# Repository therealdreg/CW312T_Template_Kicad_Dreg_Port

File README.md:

# CW312T_Template_Kicad_Dreg_Port

chipwhisper CW312T template for KiCad with Dreg port (and easyeda file to import)

------

## PCB specs

- Thickness: 1.6 mm (0.062"). Required by the CW312 card-edge connector (Samtec MECF), and it's the default thickness anyway, so no extra cost.
- Edge fingers: ENIG + "gold fingers" (solder mask removed over the pads) is enough for a target plugged in/out a few dozen times. Note JLCPCB only does "gold fingers" with ENIG selected, this is NOT real electroplated hard gold. Use real hard gold (e.g. PCBWay) only if you need hundreds/thousands of insertions.
- Bevel/chamfer (30°): JLCPCB won't bevel boards smaller than 50 x 50 mm, and can't bevel V-cut panelized fingers. Fine to skip on small targets, the MECF socket has its own lead-in.

-----

# kicad project 

[CW312T_Template_Kicad_Dreg_Port.zip](CW312T_Template_Kicad_Dreg_Port.zip)

------

# easyeda pro file to import

[ProPrj_CW312T_Template_Kicad_Dreg_Port_2026-06-29.epro2](ProPrj_CW312T_Template_Kicad_Dreg_Port_2026-06-29.epro2)

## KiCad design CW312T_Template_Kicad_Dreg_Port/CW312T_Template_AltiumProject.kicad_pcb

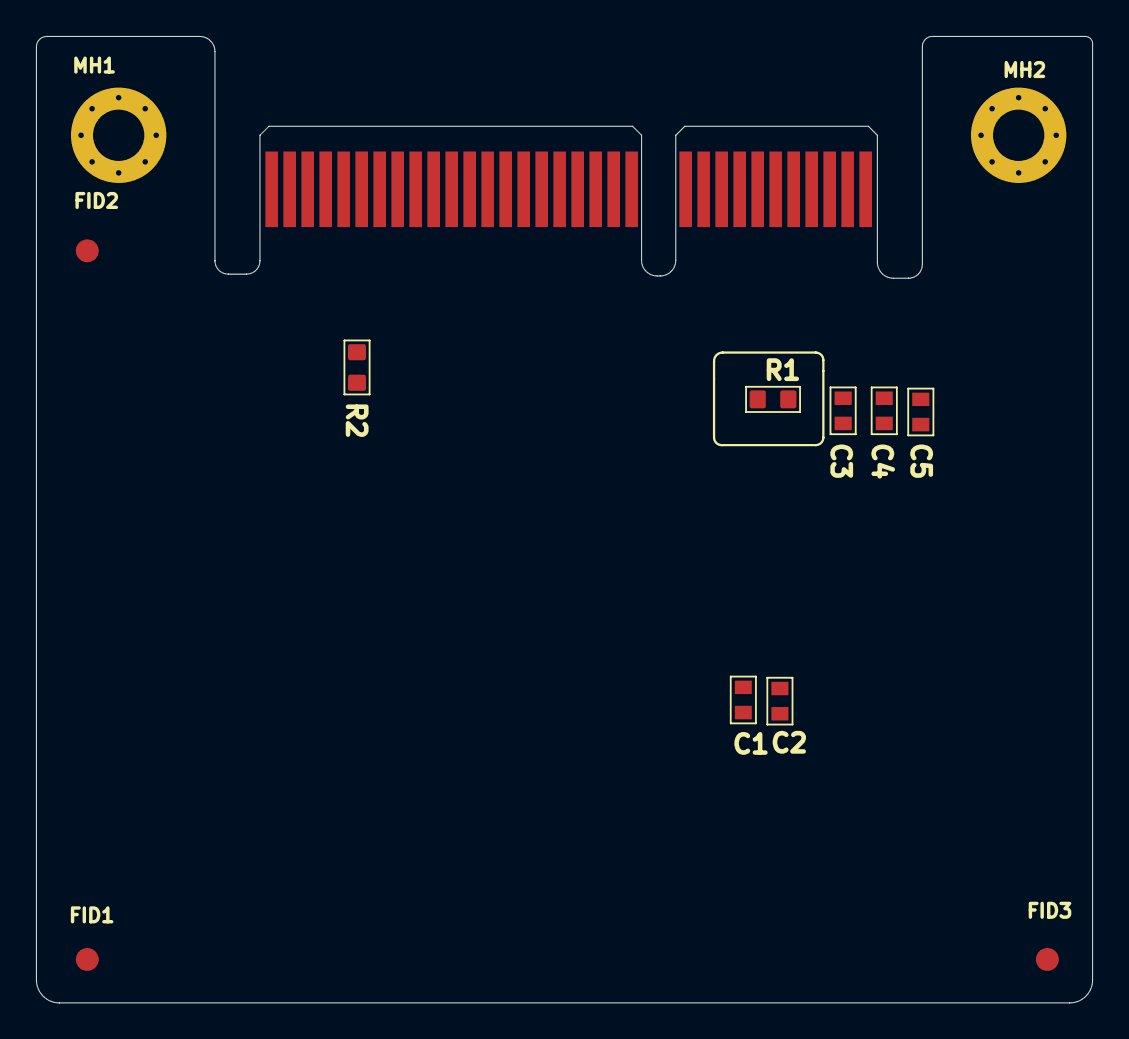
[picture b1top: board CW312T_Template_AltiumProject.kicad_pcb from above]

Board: 2 copper layers, 58.7 x 53.7 mm, 13 parts (0 on the bottom side), 6 nets, no tracks yet.

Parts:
C1, C2: DNM; CAPC0603_M
C3, C4: 100n; CAPC0603_M
C5: 2u2; CAPC0603_M
FID1, FID2, FID3: FIDU-ROUND-1.0MM; FIDU-ROUND-1.0mm
MH1, MH2: 4-40 MH, Tight Fit; MOUNT_#4_TIGHT
P1: PCIeX4-GF-2D-1000-1K-O64
R1, R2: 10R; RESC1608X55N

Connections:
CLKIN: P1.B27, R2.1
FILT_HP: C3.1, C4.1, C5.1, P1.A3, P1.B2, P1.B4, R1.2
GND: C1.2, C2.2, C3.2, C4.2, C5.2, MH1.1, MH2.1, P1.A1, P1.A2, P1.A8, P1.A20, P1.A27, P1.A28, P1.B3, P1.B9, P1.B15, P1.B21, P1.B22
IOVREF: P1.A5, P1.A26, P1.B10
SHUNTL: C1.1, C2.1, P1.B1, R1.1
nRST: P1.A31, P1.B14

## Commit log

2026-06-29 first version
2026-06-29 Modify FUNDING.yml with new funding details
    Updated funding sources with specific usernames and links.
2026-06-29 Add PCB specs section to README
    Added PCB specifications to the README.
2026-06-29 Revise PCB specs in README.md
    Updated PCB specifications for connector requirements and edge fingers.

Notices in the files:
parts and their libraries:
PRJLICENSE: TBD
